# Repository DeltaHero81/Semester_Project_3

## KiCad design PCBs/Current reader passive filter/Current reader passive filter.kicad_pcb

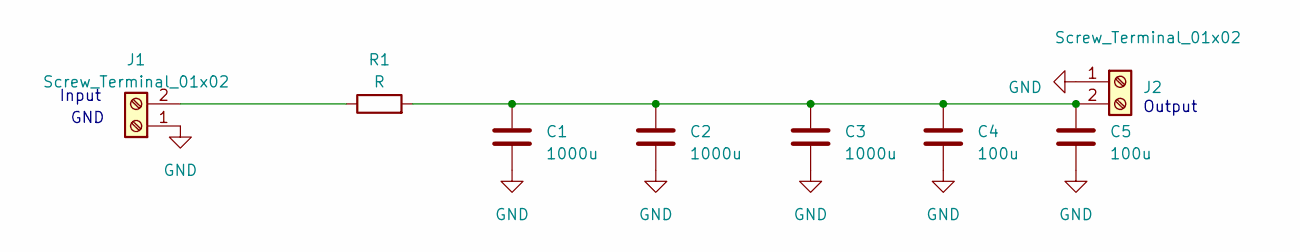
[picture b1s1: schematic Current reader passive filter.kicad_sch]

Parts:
C1, C2, C3: 1000u; CP_Radial_D10.0mm_P5.00mm
C4, C5: 100u; C_Disc_D4.7mm_W2.5mm_P5.00mm
J1, J2: Screw_Terminal_01x02; TerminalBlock_Phoenix_MKDS-3-2-5.08_1x02_P5.08mm_Horizontal
R1: R; R_Axial_DIN0207_L6.3mm_D2.5mm_P10.16mm_Horizontal

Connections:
GND: C1.2, C2.2, C3.2, C4.2, C5.2, J1.1, J2.1
unnamed: J1.2, R1.1
unnamed: C1.1, C2.1, C3.1, C4.1, C5.1, J2.2, R1.2

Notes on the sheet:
Output
Input
GND

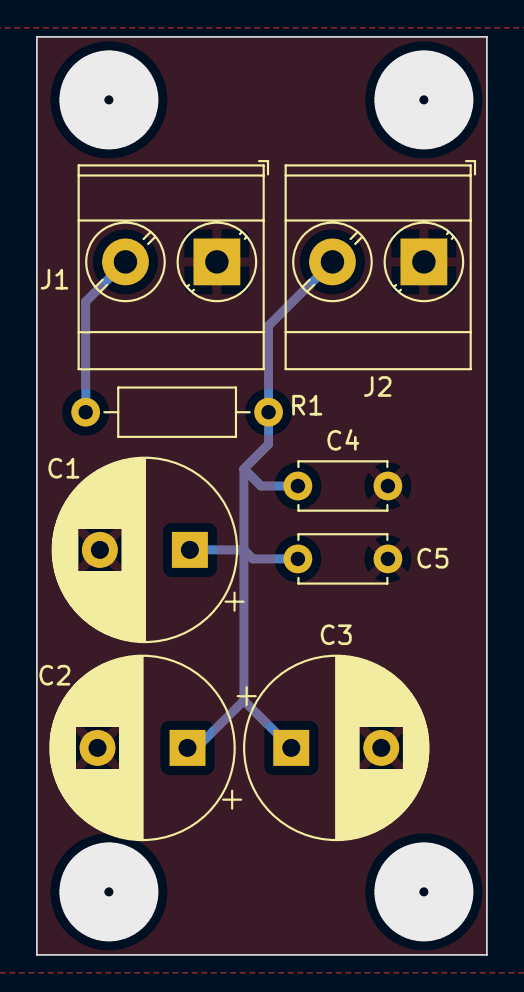
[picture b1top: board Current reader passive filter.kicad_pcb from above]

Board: 2 copper layers, 25.0 x 51.0 mm, 8 parts (0 on the bottom side), 3 nets.

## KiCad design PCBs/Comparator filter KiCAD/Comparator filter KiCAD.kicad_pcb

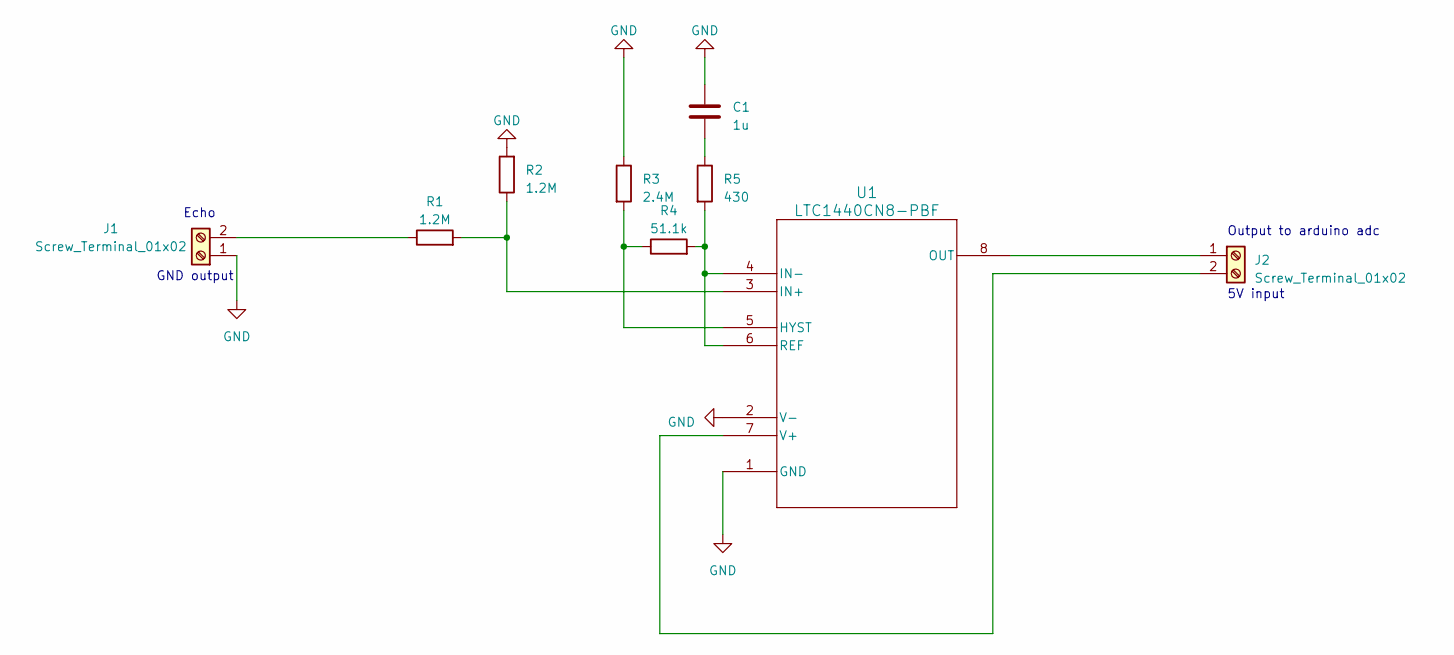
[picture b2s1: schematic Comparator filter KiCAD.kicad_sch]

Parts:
C1: 1u; CP_Radial_D10.0mm_P5.00mm
J1, J2: Screw_Terminal_01x02; TerminalBlock_Phoenix_MKDS-3-2-5.08_1x02_P5.08mm_Horizontal
R1, R2: 1.2M; R_Axial_DIN0207_L6.3mm_D2.5mm_P10.16mm_Horizontal
R3: 2.4M; R_Axial_DIN0207_L6.3mm_D2.5mm_P10.16mm_Horizontal
R4: 51.1k; R_Axial_DIN0207_L6.3mm_D2.5mm_P10.16mm_Horizontal
R5: 430; R_Axial_DIN0207_L6.3mm_D2.5mm_P10.16mm_Horizontal
U1: LTC1440CN8-PBF; PDIP-8_N_LIT

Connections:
GND: C1.1, J1.1, R2.2, R3.1, U1.1 (GND), U1.2 (V-)
unnamed: C1.2, R5.1
unnamed: J1.2, R1.1
unnamed: J2.1, U1.8 (OUT)
unnamed: J2.2, U1.7 (V+)
unnamed: R3.2, R4.1, U1.5 (HYST)
unnamed: R1.2, R2.1, U1.3 (IN+)
unnamed: R4.2, R5.2, U1.4 (IN-), U1.6 (REF)

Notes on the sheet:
Echo
GND output
5V input
Output to arduino adc

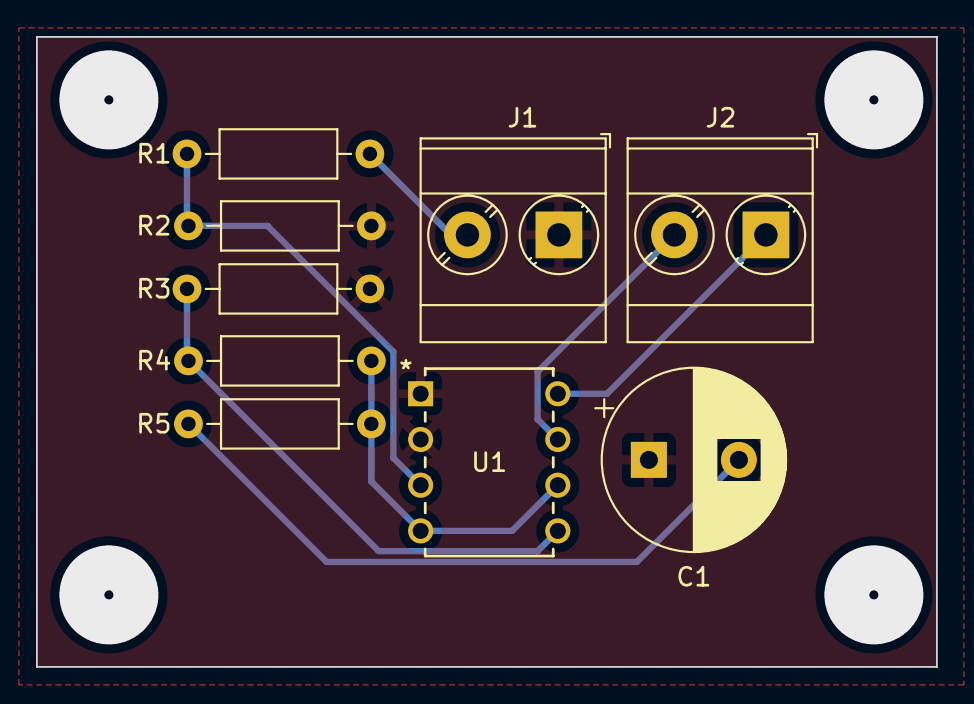
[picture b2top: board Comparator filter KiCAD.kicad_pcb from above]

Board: 2 copper layers, 50.0 x 35.0 mm, 9 parts (0 on the bottom side), 8 nets.

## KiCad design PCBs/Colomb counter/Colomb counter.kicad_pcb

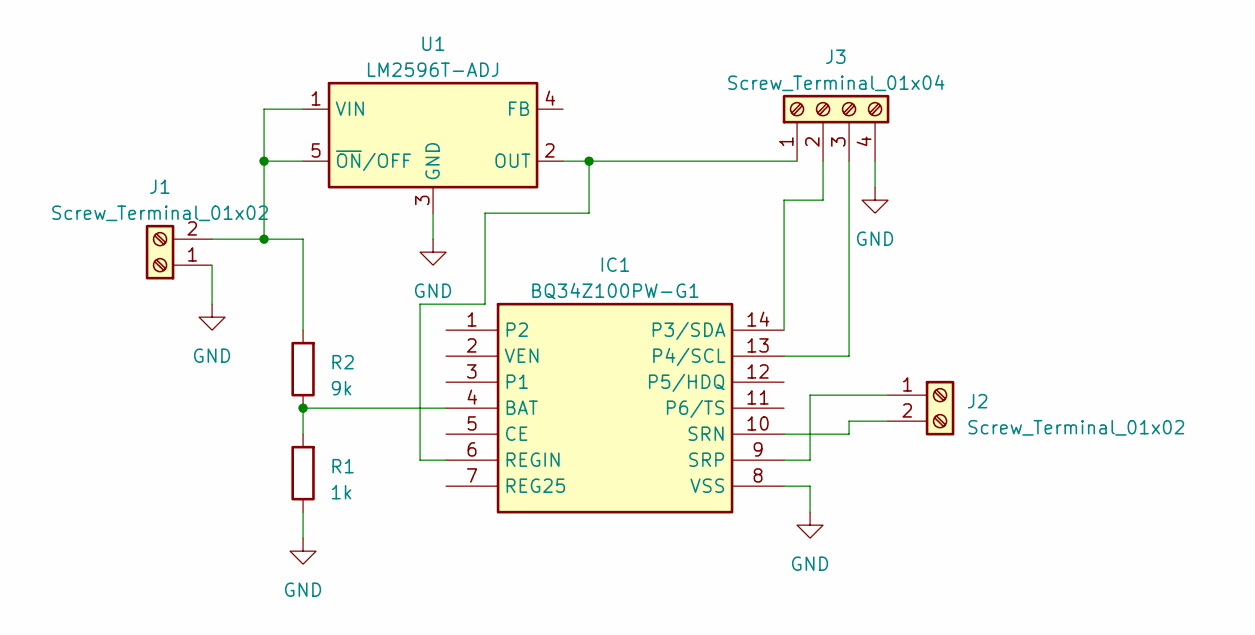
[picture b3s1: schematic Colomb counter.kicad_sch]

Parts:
IC1: BQ34Z100PW-G1; SOP65P640X120-14N; Mouser Part Number 595-BQ34Z100PW-G1
J1, J2: Screw_Terminal_01x02; TerminalBlock_Phoenix_MKDS-3-2-5.08_1x02_P5.08mm_Horizontal
J3: Screw_Terminal_01x04; TerminalBlock_Phoenix_MKDS-1,5-4_1x04_P5.00mm_Horizontal
R1: 1k; R_Axial_DIN0207_L6.3mm_D2.5mm_P10.16mm_Horizontal
R2: 9k; R_Axial_DIN0207_L6.3mm_D2.5mm_P10.16mm_Horizontal
U1: LM2596T-ADJ; TO-220-5_P3.4x3.7mm_StaggerOdd_Lead3.8mm_Vertical

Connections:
GND: IC1.8 (VSS), J1.1, J3.4, R1.1, U1.3 (GND)
unnamed: IC1.4 (BAT), R1.2, R2.1
unnamed: IC1.14 (P3/SDA), J3.2
unnamed: IC1.13 (P4/SCL), J3.3
unnamed: IC1.6 (REGIN), J3.1, U1.2 (OUT)
unnamed: IC1.10 (SRN), J2.2
unnamed: IC1.9 (SRP), J2.1
unnamed: J1.2, R2.2, U1.1 (VIN), U1.5 (~ON/OFF)

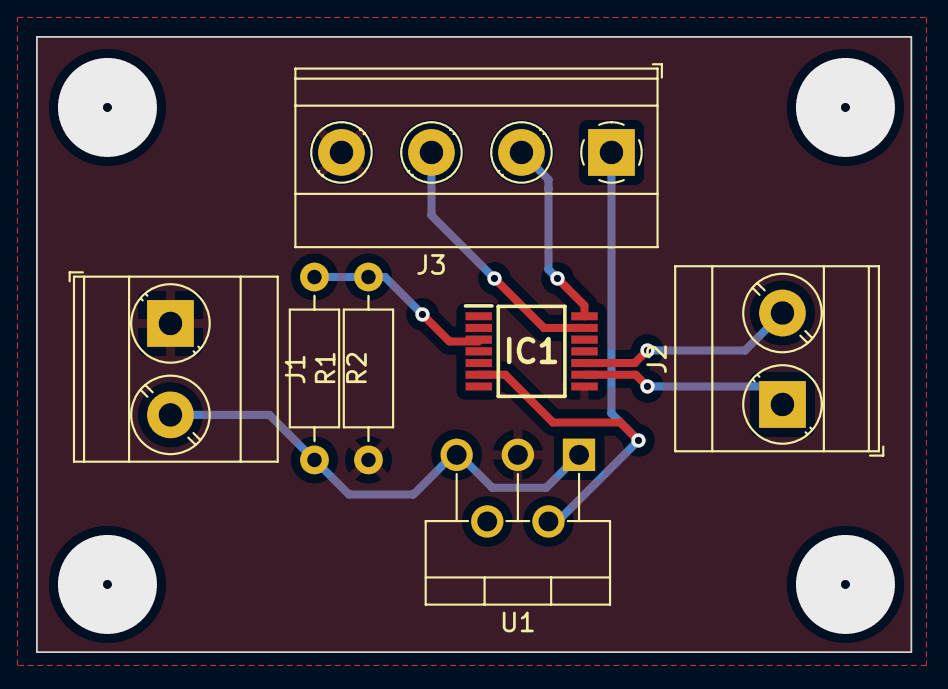
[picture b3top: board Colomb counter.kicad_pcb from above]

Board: 2 copper layers, 48.6 x 34.2 mm, 7 parts (0 on the bottom side), 8 nets.

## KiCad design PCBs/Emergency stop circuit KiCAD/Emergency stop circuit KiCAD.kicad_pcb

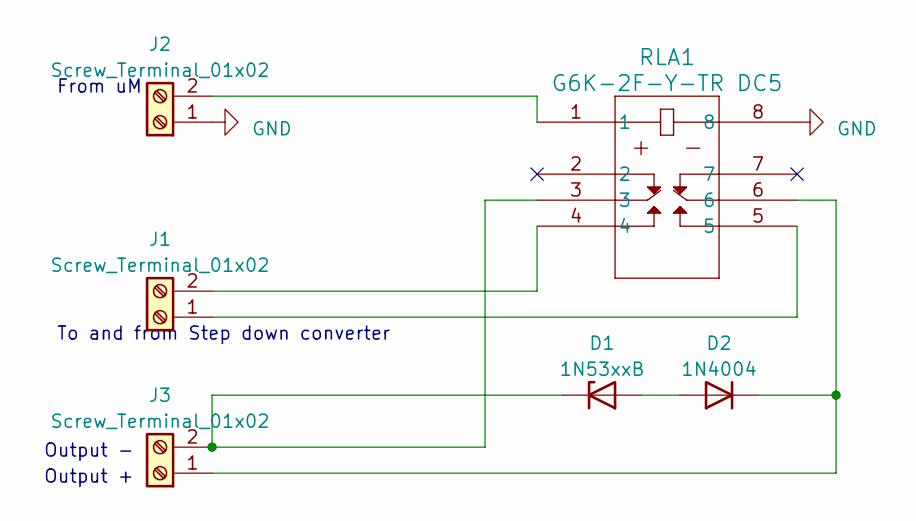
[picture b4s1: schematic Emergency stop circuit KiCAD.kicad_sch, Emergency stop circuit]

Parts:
D1: 1N53xxB; D_DO-201_P15.24mm_Horizontal
D2: 1N4004; D_DO-41_SOD81_P10.16mm_Horizontal
J1, J2, J3: Screw_Terminal_01x02; TerminalBlock_Phoenix_MKDS-3-2-5.08_1x02_P5.08mm_Horizontal
RLA1: G6K-2F-Y-TR DC5; G6K-2F-Y DC3

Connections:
GND: J2.1, RLA1.8
unnamed: D1.2 (A), D2.2 (A)
unnamed: D1.1 (K), J3.2, RLA1.3
unnamed: D2.1 (K), J3.1, RLA1.6
unnamed: J1.1, RLA1.5
unnamed: J1.2, RLA1.4
unnamed: J2.2, RLA1.1

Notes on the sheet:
From uM
Output -
To and from Step down converter
Output +

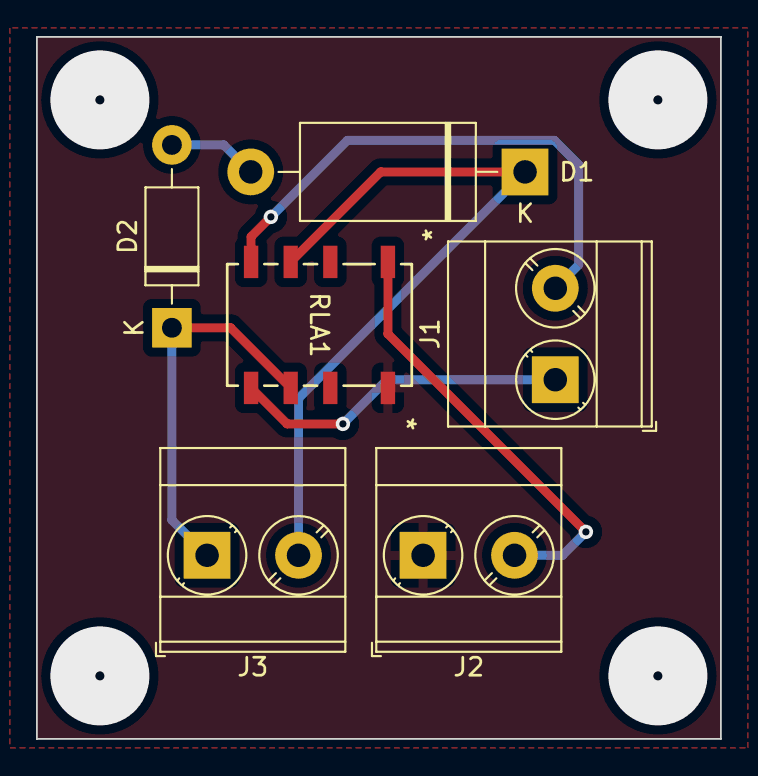
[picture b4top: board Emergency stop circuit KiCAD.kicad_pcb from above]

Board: 2 copper layers, 38.0 x 39.0 mm, 6 parts (0 on the bottom side), 7 nets.

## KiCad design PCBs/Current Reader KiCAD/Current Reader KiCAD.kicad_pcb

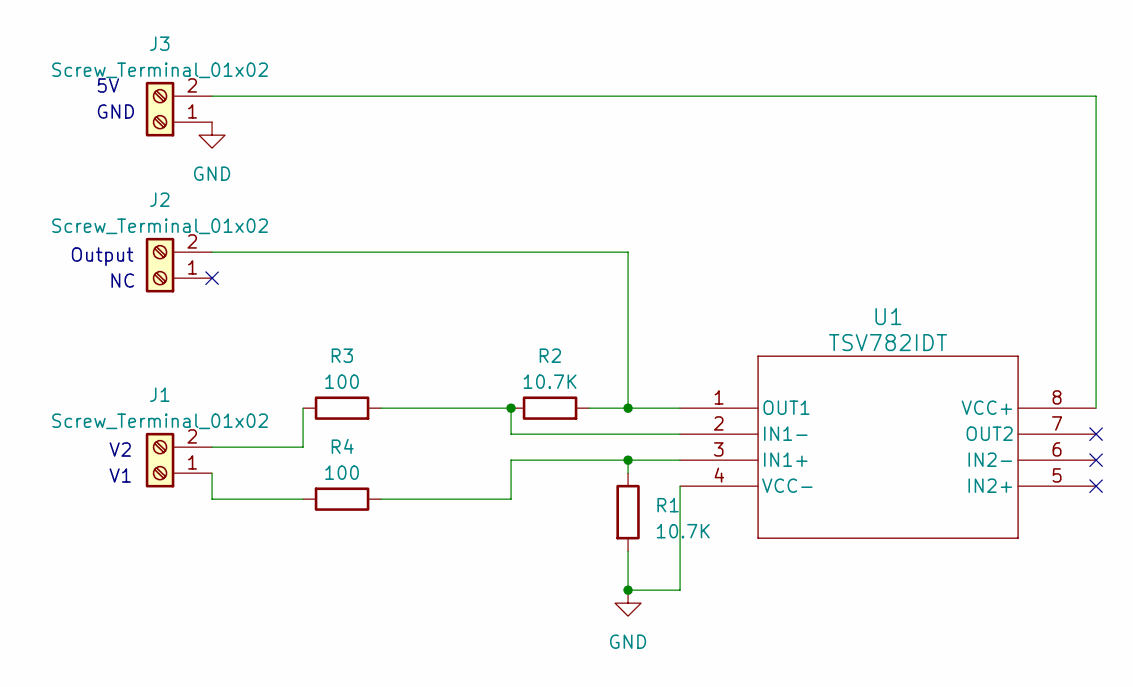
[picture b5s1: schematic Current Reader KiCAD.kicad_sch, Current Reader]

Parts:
J1, J2, J3: Screw_Terminal_01x02; TerminalBlock_Phoenix_MKDS-3-2-5.08_1x02_P5.08mm_Horizontal
R1, R2: 10.7K; R_Axial_DIN0207_L6.3mm_D2.5mm_P10.16mm_Horizontal
R3, R4: 100; R_Axial_DIN0207_L6.3mm_D2.5mm_P10.16mm_Horizontal
U1: TSV782IDT; SO8_4X5X1P27_STM

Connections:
GND: J3.1, R1.2, U1.4 (VCC-)
unnamed: J1.1, R4.2
unnamed: J1.2, R3.1
unnamed: J2.2, R2.2, U1.1 (OUT1)
unnamed: J3.2, U1.8 (VCC+)
unnamed: R1.1, R4.1, U1.3 (IN1+)
unnamed: R2.1, R3.2, U1.2 (IN1-)

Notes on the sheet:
GND
Output

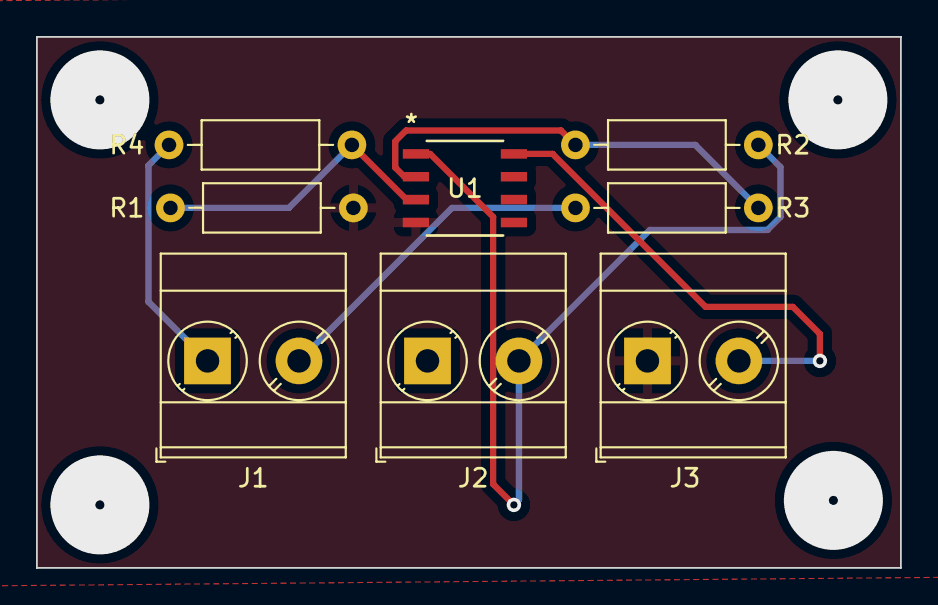
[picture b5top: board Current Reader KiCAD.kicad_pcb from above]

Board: 2 copper layers, 48.0 x 29.5 mm, 8 parts (0 on the bottom side), 7 nets.
